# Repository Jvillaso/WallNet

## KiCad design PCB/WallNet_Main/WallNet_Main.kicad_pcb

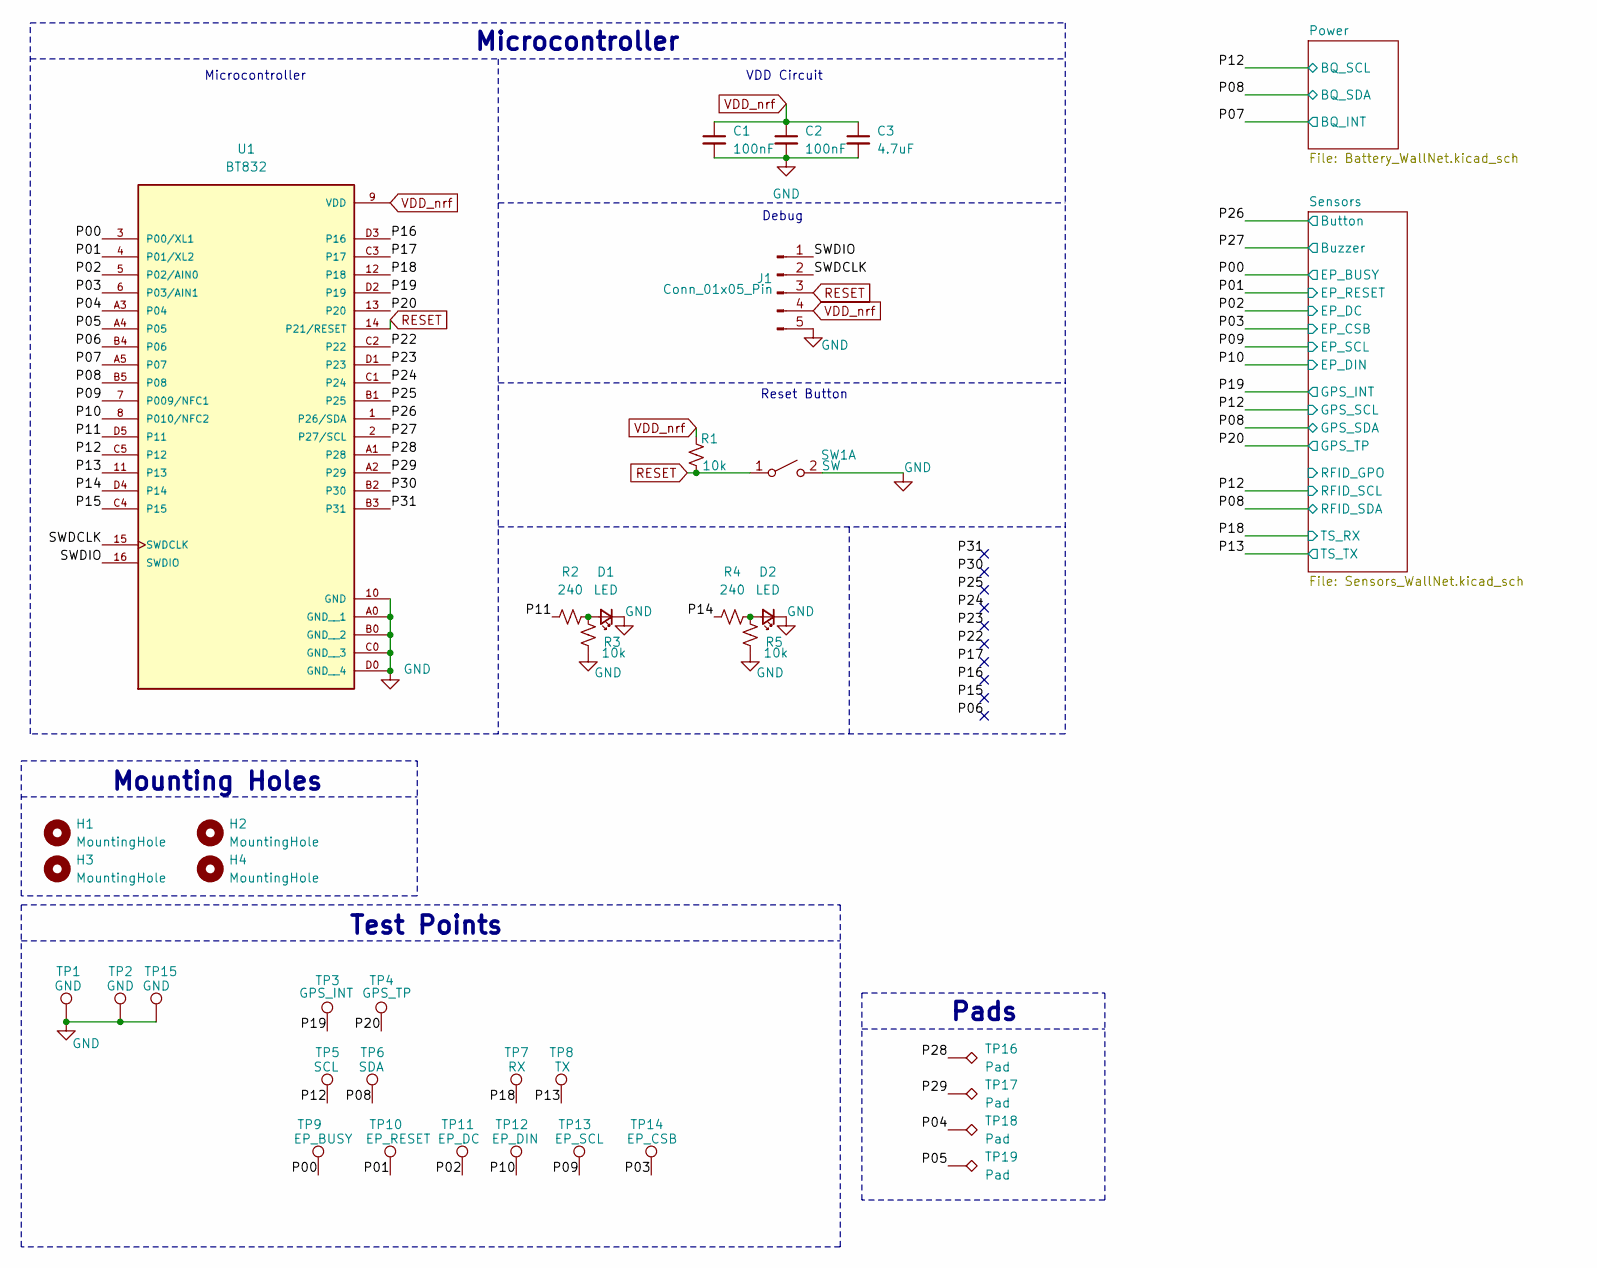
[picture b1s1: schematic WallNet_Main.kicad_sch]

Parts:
C1, C2: 100nF; C_0603_1608Metric
C3: 4.7uF; C_0805_2012Metric
D1, D2: LED; D_0603_1608Metric
H1, H2, H3, H4: MountingHole; MountingHole_4.3mm_M4
J1: Conn_01x05_Pin; PinHeader_1x05_P2.54mm_Vertical
R1, R3, R5: 10k; R_0603_1608Metric
R2, R4: 240; R_0603_1608Metric
SW1: SW; SW_Push_1P1T_NO_E-Switch_TL3301NxxxxxG
TP1: GND; TestPoint_Pad_D1.0mm
TP2, TP15: GND; KEYSTONE_5001
TP3: GPS_INT; KEYSTONE_5001
TP4: GPS_TP; KEYSTONE_5001
TP5: SCL; KEYSTONE_5001
TP6: SDA; KEYSTONE_5001
TP7: RX; KEYSTONE_5001
TP8: TX; KEYSTONE_5001
TP9: EP_BUSY; KEYSTONE_5001
TP10: EP_RESET; KEYSTONE_5001
TP11: EP_DC; KEYSTONE_5001
TP12: EP_DIN; KEYSTONE_5001
TP13: EP_SCL; KEYSTONE_5001
TP14: EP_CSB; KEYSTONE_5001
TP16, TP17, TP18, TP19: Pad; TestPoint_Pad_1.0x1.0mm
U1: BT832; BLEMODULE_BT832; PARTREV 2.04

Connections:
/P00: TP9.1, U1.3 (P00/XL1); also elsewhere on the board
/P01: TP10.1, U1.4 (P01/XL2); also elsewhere on the board
/P02: TP11.1, U1.5 (P02/AIN0); also elsewhere on the board
/P03: TP14.1, U1.6 (P03/AIN1); also elsewhere on the board
/P04: TP18.1, U1.A3 (P04)
/P05: TP19.1, U1.A4 (P05)
/P06: U1.B4 (P06)
/P07: U1.A5 (P07); also elsewhere on the board
/P08: TP6.1, U1.B5 (P08); also elsewhere on the board
/P09: TP13.1, U1.7 (P009/NFC1); also elsewhere on the board
/P10: TP12.1, U1.8 (P010/NFC2); also elsewhere on the board
/P11: R2.1, U1.D5 (P11)
/P12: TP5.1, U1.C5 (P12); also elsewhere on the board
/P13: TP8.1, U1.11 (P13); also elsewhere on the board
/P14: R4.1, U1.D4 (P14)
/P15: U1.C4 (P15)
/P16: U1.D3 (P16)
/P17: U1.C3 (P17)
/P18: TP7.1, U1.12 (P18); also elsewhere on the board
/P19: TP3.1, U1.D2 (P19); also elsewhere on the board
/P20: TP4.1, U1.13 (P20); also elsewhere on the board
/P22: U1.C2 (P22)
/P23: U1.D1 (P23)
/P24: U1.C1 (P24)
/P25: U1.B1 (P25)
/P26: U1.1 (P26/SDA); also elsewhere on the board
/P27: U1.2 (P27/SCL); also elsewhere on the board
/P28: TP16.1, U1.A1 (P28)
/P29: TP17.1, U1.A2 (P29)
/P30: U1.B2 (P30)
/P31: U1.B3 (P31)
/SWDCLK: J1.2, U1.15 (SWDCLK)
/SWDIO: J1.1, U1.16 (SWDIO)
GND: C1.2, C2.2, C3.2, D1.1 (K), D2.1 (K), J1.5, R3.1, R5.1, SW1.2 (B), TP1.1, TP2.1, TP15.1, U1.10 (GND), U1.A0 (GND__1), U1.B0 (GND__2), U1.C0 (GND__3), U1.D0 (GND__4); also elsewhere on the board
unnamed: D1.2 (A), R2.2, R3.2
unnamed: D2.2 (A), R4.2, R5.2
RESET: J1.3, R1.2, SW1.1 (A), U1.14 (P21/RESET); also elsewhere on the board
VDD_nrf: C1.1, C2.1, C3.1, J1.4, R1.1, U1.9 (VDD); also elsewhere on the board

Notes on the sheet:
Mounting Holes
Debug
Microcontroller
VDD Circuit
Test Points
Pads
Reset Button
Microcontroller

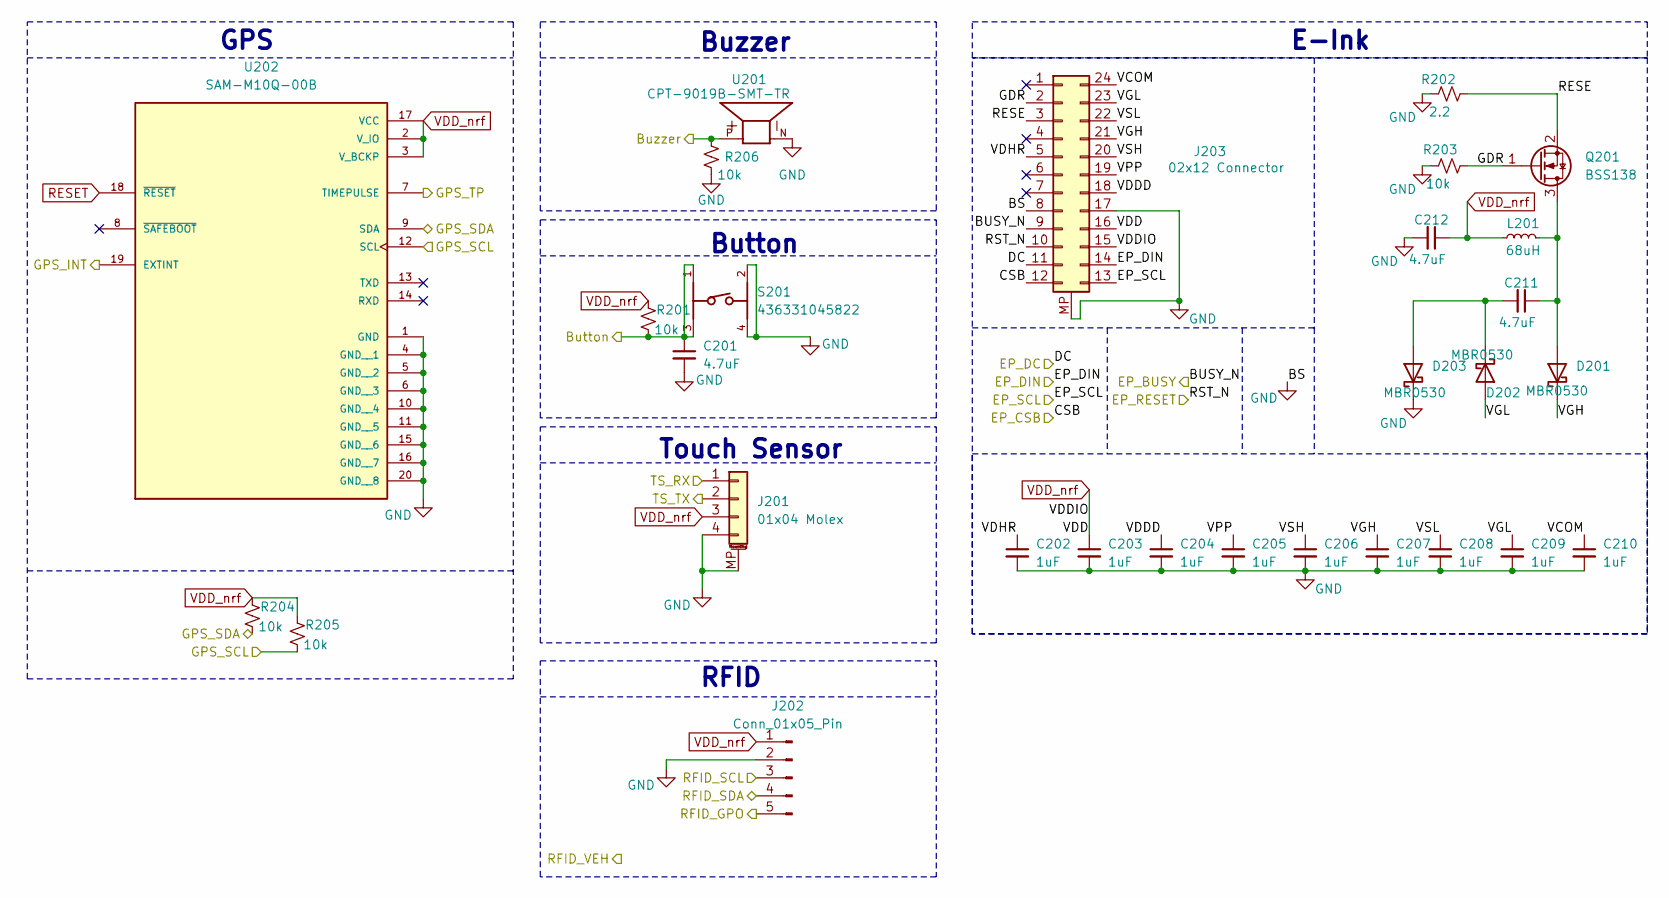
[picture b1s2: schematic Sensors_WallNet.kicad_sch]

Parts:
C201, C211, C212: 4.7uF; C_0603_1608Metric
C202, C203, C204, C205, C206, C207, C208, C209, C210: 1uF; C_0603_1608Metric
D201, D202, D203: MBR0530; D_SOD-123
J201: 01x04 Molex; Molex_PicoBlade_53261-0471_1x04-1MP_P1.25mm_Horizontal
J202: Conn_01x05_Pin; PinHeader_1x05_P2.54mm_Vertical
J203: 02x12 Connector; Amphenol_F32Q-1A7x1-11024_1x24-1MP_P0.5mm_Horizontal
L201: 68uH; IND_VLS3015CX-680M-H
Q201: BSS138; SOT-23
R201, R203, R204, R205, R206: 10k; R_0603_1608Metric
R202: 2.2; R_0603_1608Metric
S201: 436331045822; 4363X10458XX
U201: CPT-9019B-SMT-TR; XDCR_CPT-9019B-SMT-TR; PARTREV 1.0
U202: SAM-M10Q-00B; XCVR_SAM-M10Q-00B; PARTREV R03

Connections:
/P00: J203.9; also elsewhere on the board
/P01: J203.10; also elsewhere on the board
/P02: J203.11; also elsewhere on the board
/P03: J203.12; also elsewhere on the board
/P08: J202.4, R204.2, U202.9 (SDA); also elsewhere on the board
/P09: J203.13; also elsewhere on the board
/P10: J203.14; also elsewhere on the board
/P12: J202.3, R205.2, U202.12 (SCL); also elsewhere on the board
/P13: J201.2; also elsewhere on the board
/P18: J201.1; also elsewhere on the board
/P19: U202.19 (EXTINT); also elsewhere on the board
/P20: U202.7 (TIMEPULSE); also elsewhere on the board
/P26: C201.1, R201.2, S201.1, S201.3; also elsewhere on the board
/P27: R206.1, U201.P; also elsewhere on the board
/Sensors/GDR: J203.2, Q201.1 (G), R203.2
/Sensors/RESE: J203.3, Q201.2 (S), R202.2
/Sensors/RFID_GPO: J202.5
/Sensors/VCOM: C210.1, J203.24
/Sensors/VDDD: C204.1, J203.18
/Sensors/VDHR: C202.1, J203.5
/Sensors/VGH: C207.1, D201.1 (K), J203.21
/Sensors/VGL: C209.1, D202.2 (A), J203.23
/Sensors/VPP: C205.1, J203.19
/Sensors/VSH: C206.1, J203.20
/Sensors/VSL: C208.1, J203.22
GND: C201.2, C202.2, C203.2, C204.2, C205.2, C206.2, C207.2, C208.2, C209.2, C210.2, C212.2, D203.1 (K), J201.4, J201.MP (MountPin), J202.2, J203.8, J203.17, J203.MP (Pin_12), R202.1, R203.1, R206.2, S201.2, S201.4, U201.N, U202.1 (GND), U202.4 (GND__1), U202.5 (GND__2), U202.6 (GND__3), U202.10 (GND__4), U202.11 (GND__5), U202.15 (GND__6), U202.16 (GND__7), U202.20 (GND__8); also elsewhere on the board
unnamed: C211.1, D201.2 (A), L201.2, Q201.3 (D)
unnamed: C211.2, D202.1 (K), D203.2 (A)
RESET: U202.18 (~RESET); also elsewhere on the board
VDD_nrf: C203.1, C212.1, J201.3, J202.1, J203.15, J203.16, L201.1, R201.1, R204.1, R205.1, U202.2 (V_IO), U202.3 (V_BCKP), U202.17 (VCC); also elsewhere on the board

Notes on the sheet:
RFID
E-Ink
GPS
Button
Touch Sensor
Buzzer

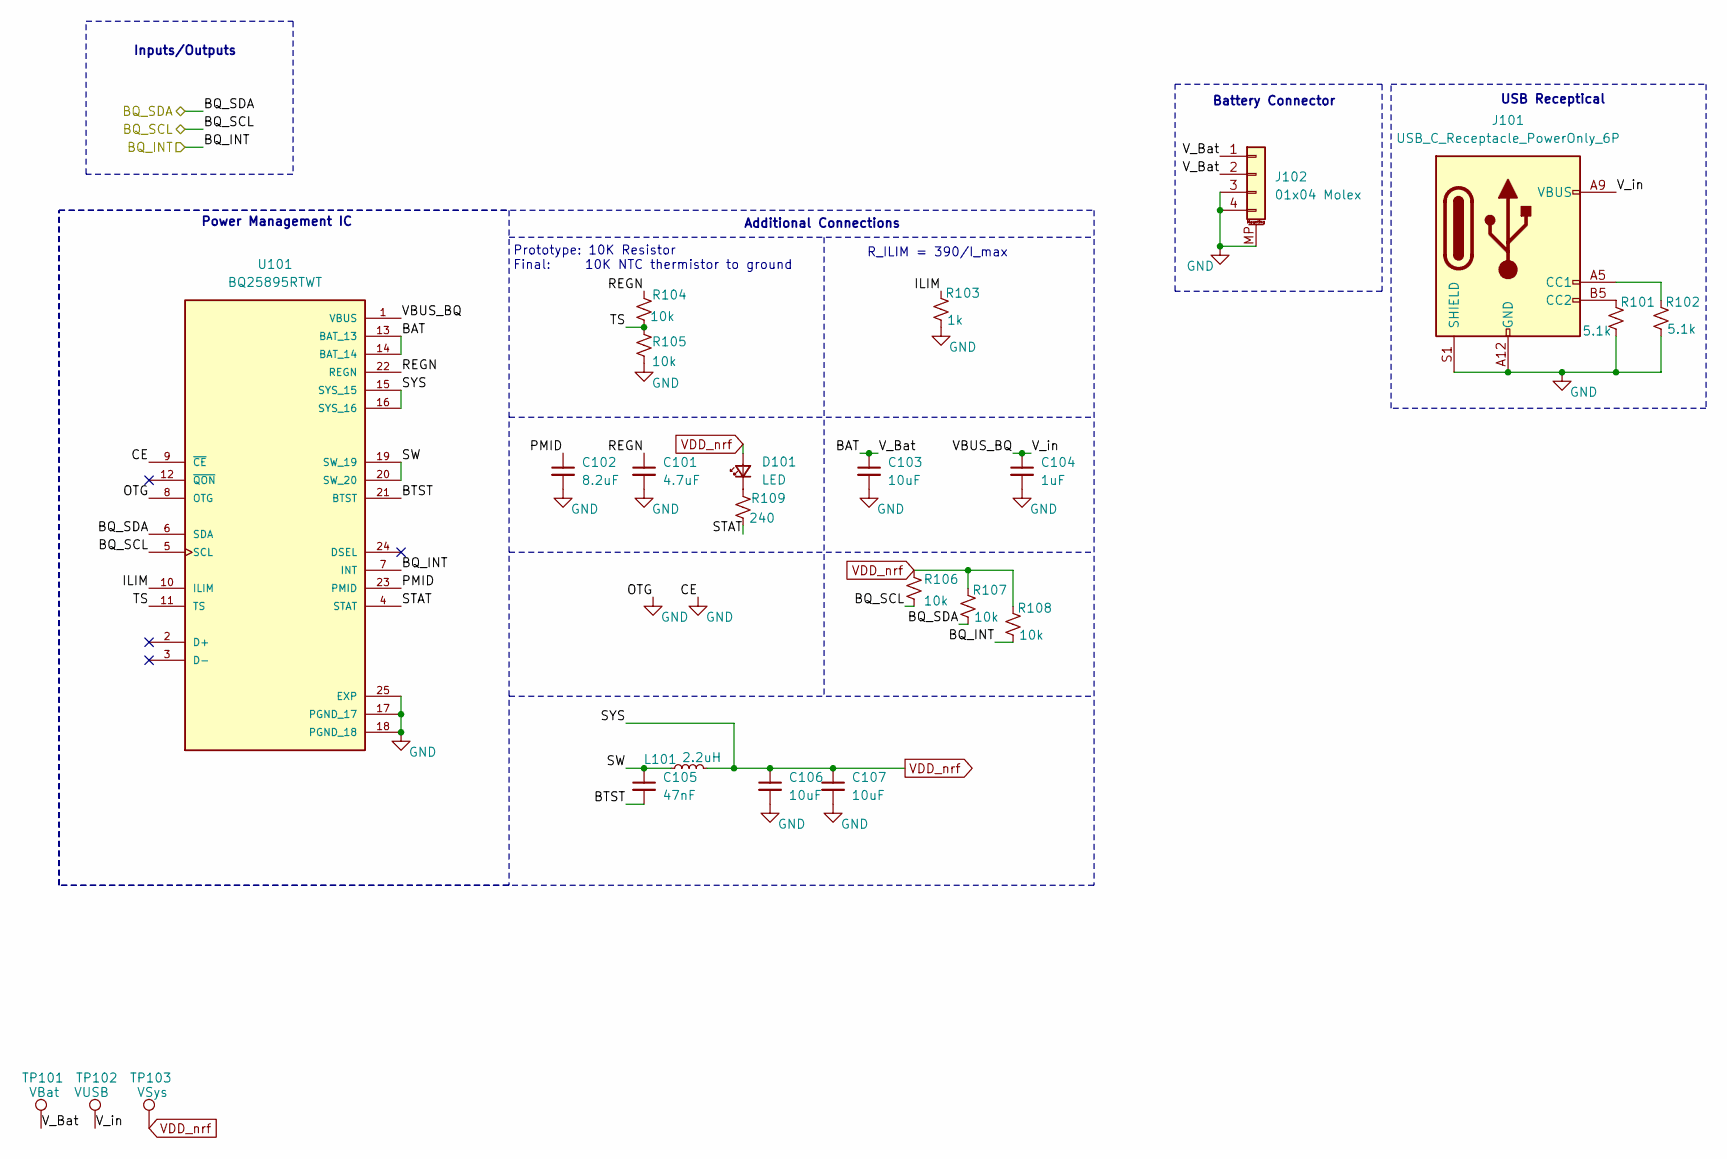
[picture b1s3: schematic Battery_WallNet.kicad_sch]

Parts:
C101: 4.7uF; C_0603_1608Metric
C102: 8.2uF; C_0805_2012Metric
C103: 10uF; C_0805_2012Metric
C104: 1uF; C_0603_1608Metric
C105: 47nF; C_0603_1608Metric
C106, C107: 10uF; C_0603_1608Metric
D101: LED; D_0603_1608Metric
J101: USB_C_Receptacle_PowerOnly_6P; USB_C_Receptacle_GCT_USB4125-xx-x-0190_6P_TopMnt_Horizontal
J102: 01x04 Molex; Molex_PicoBlade_53261-0471_1x04-1MP_P1.25mm_Horizontal
L101: 2.2uH; IND_IMSC1008AZER_VIS
R101, R102: 5.1k; R_0603_1608Metric
R103: 1k; R_0603_1608Metric
R104, R105, R106, R107, R108: 10k; R_0603_1608Metric
R109: 240; R_0603_1608Metric
TP101: VBat; TestPoint_Pad_D1.0mm
TP102: VUSB; TestPoint_Pad_D1.0mm
TP103: VSys; TestPoint_Pad_D1.0mm
U101: BQ25895RTWT; Texas_RTW_WQFN-24-1EP_4x4mm_P0.5mm_EP2.7x2.7mm; PARTREV B

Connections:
/P07: R108.2, U101.7 (INT); also elsewhere on the board
/P08: R107.2, U101.6 (SDA); also elsewhere on the board
/P12: R106.2, U101.5 (SCL); also elsewhere on the board
/Power/BAT: C103.1, J102.1, J102.2, TP101.1, U101.13 (BAT_13), U101.14 (BAT_14)
/Power/BTST: C105.2, U101.21 (BTST)
/Power/ILIM: R103.1, U101.10 (ILIM)
/Power/PMID: C102.1, U101.23 (PMID)
/Power/REGN: C101.1, R104.1, U101.22 (REGN)
/Power/STAT: R109.2, U101.4 (STAT)
/Power/SW: C105.1, L101.1, U101.19 (SW_19), U101.20 (SW_20)
/Power/TS: R104.2, R105.1, U101.11 (TS)
/Power/VBUS_BQ: C104.1, J101.A9 (VBUS), J101.B9 (VBUS), TP102.1, U101.1 (VBUS)
GND: C101.2, C102.2, C103.2, C104.2, C106.2, C107.2, J101.A12 (GND), J101.B12 (GND), J101.S1 (SHIELD), J102.3, J102.4, J102.MP (MountPin), R101.2, R102.2, R103.2, R105.2, U101.8 (OTG), U101.9 (~CE), U101.17 (PGND_17), U101.18 (PGND_18), U101.25 (EXP); also elsewhere on the board
unnamed: D101.1 (K), R109.1
unnamed: J101.A5 (CC1), R102.1
unnamed: J101.B5 (CC2), R101.1
VDD_nrf: C106.1, C107.1, D101.2 (A), L101.2, R106.1, R107.1, R108.1, TP103.1, U101.15 (SYS_15), U101.16 (SYS_16); also elsewhere on the board

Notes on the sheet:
Battery Connector
USB Receptical
Prototype: 10K Resistor Final: 10K NTC thermistor to ground
Additional Connections
Power Management IC
R_ILIM = 390/I_max
Inputs/Outputs

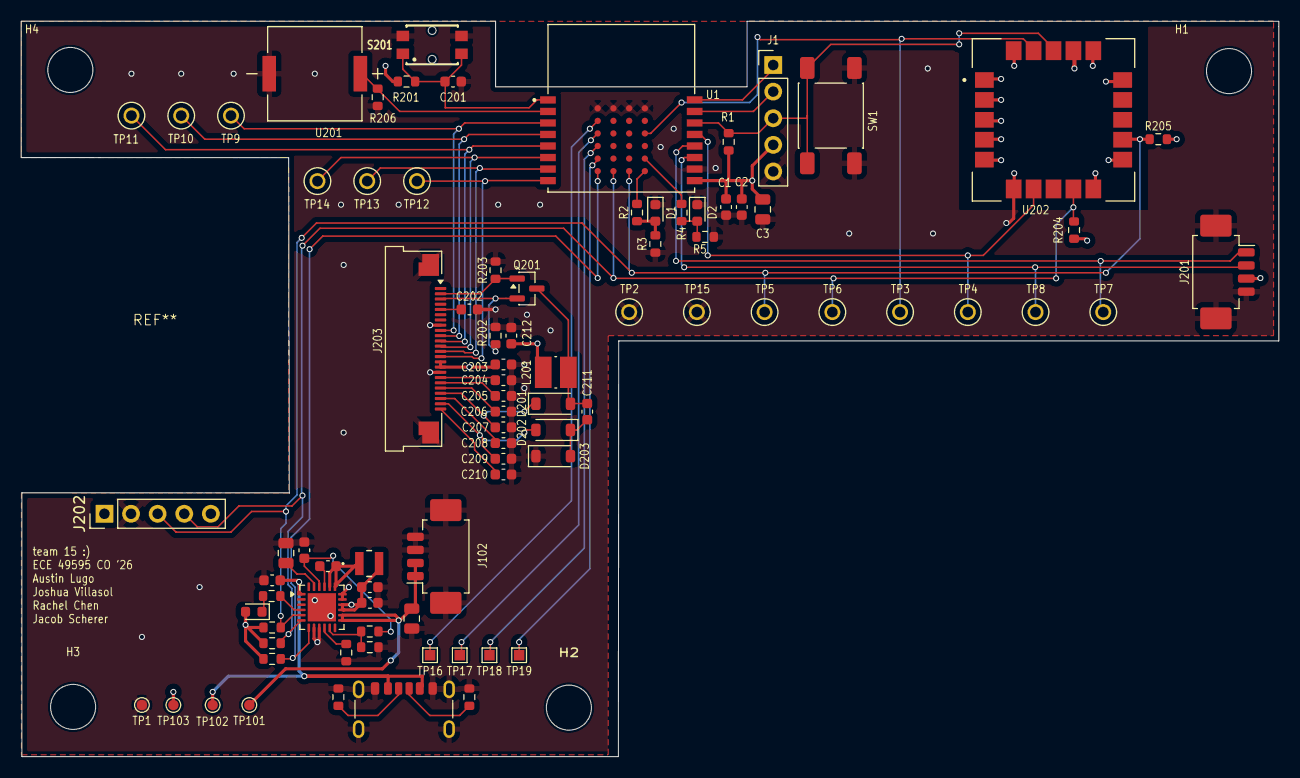
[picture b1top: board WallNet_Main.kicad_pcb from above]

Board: 4 copper layers, 120.0 x 70.2 mm, 89 parts (0 on the bottom side), 52 nets.

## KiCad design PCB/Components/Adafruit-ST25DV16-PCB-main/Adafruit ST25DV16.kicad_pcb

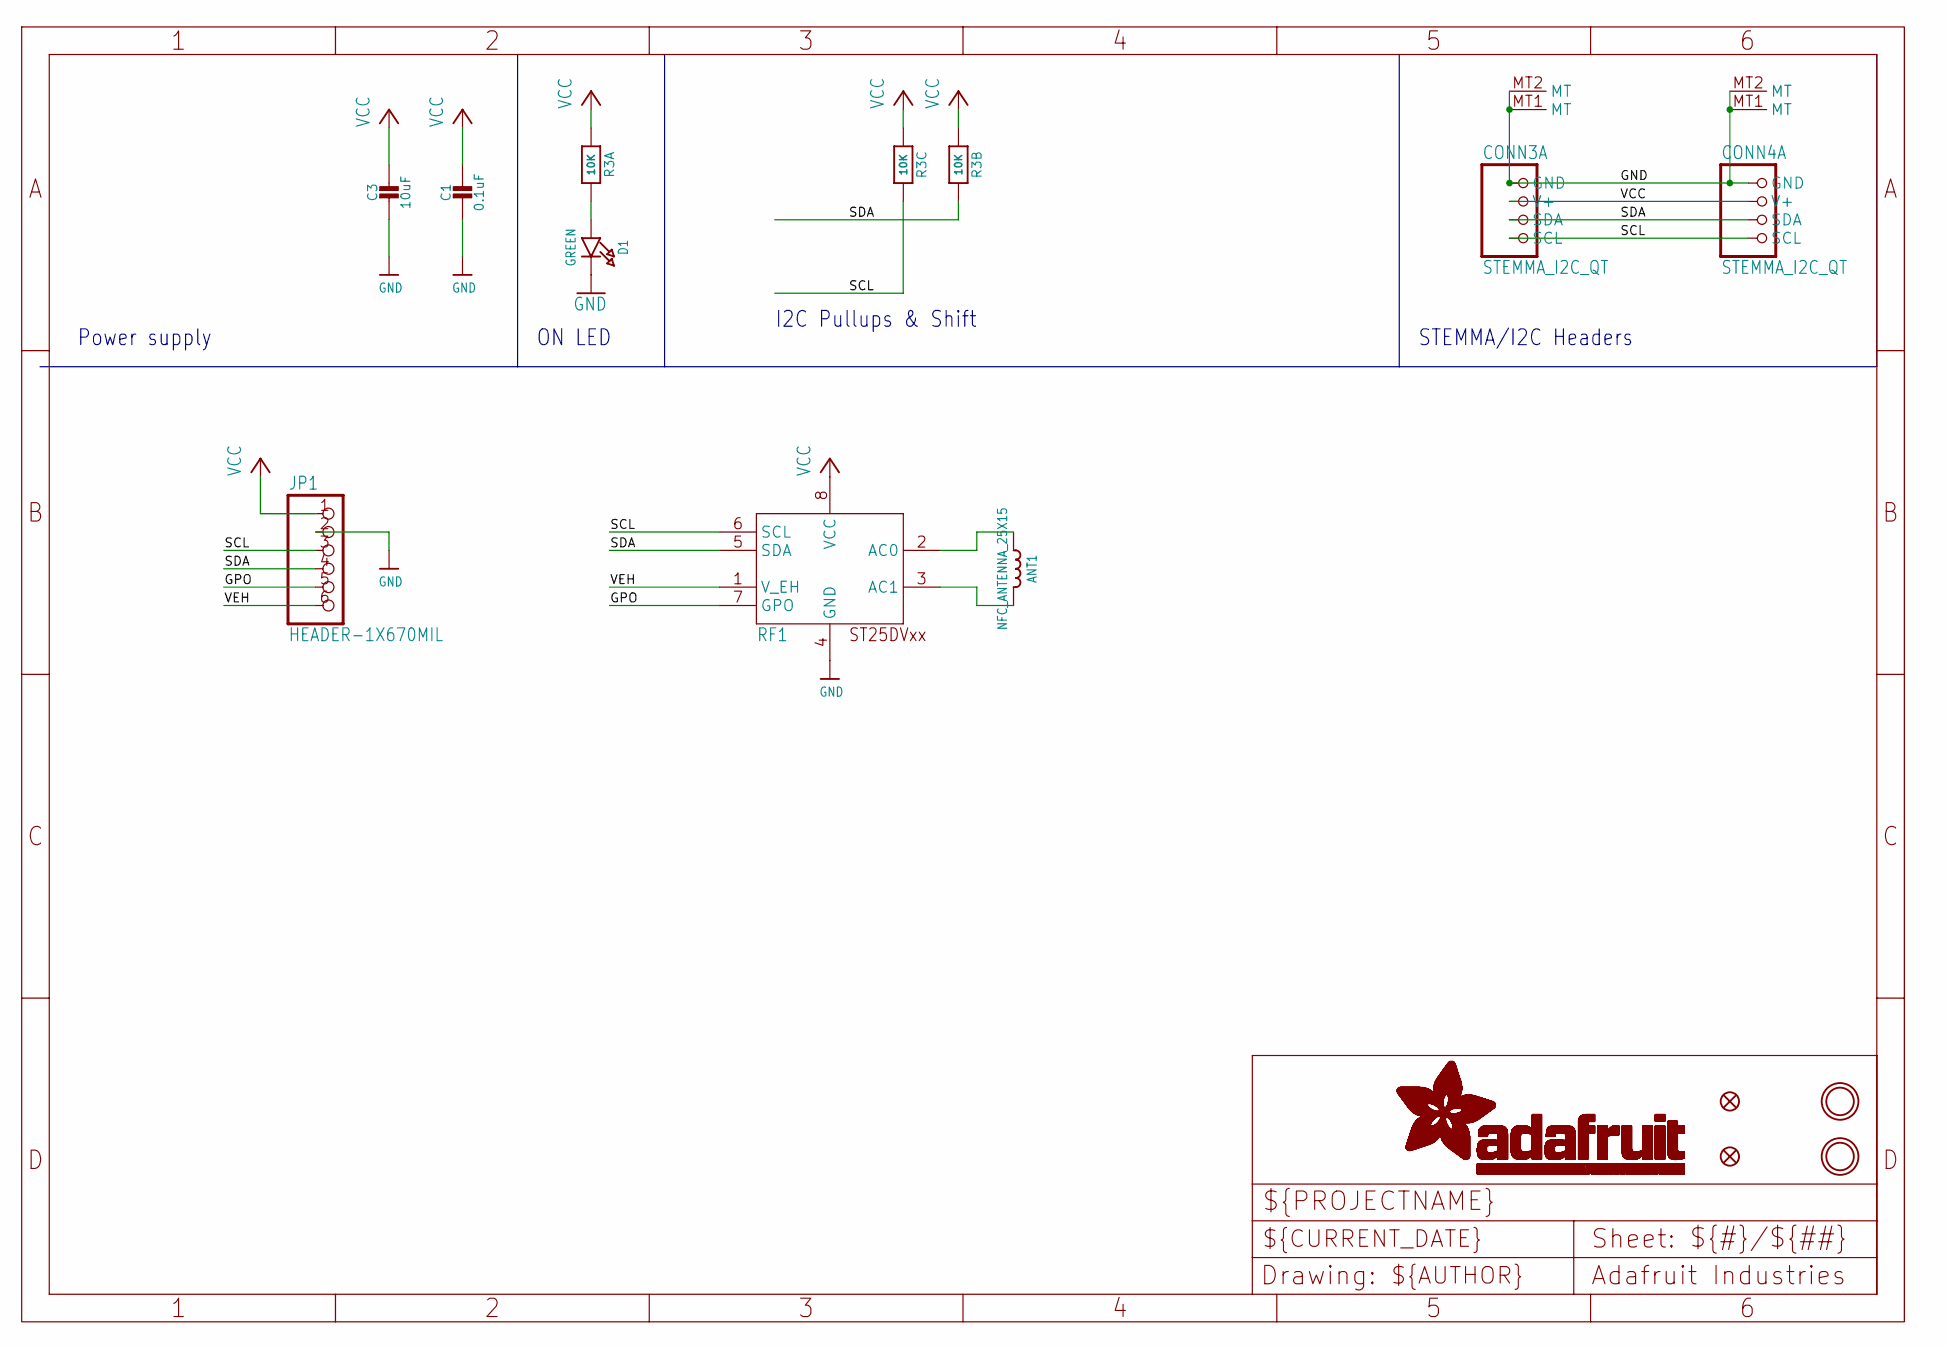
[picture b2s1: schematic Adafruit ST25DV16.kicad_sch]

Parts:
ANT1: NFC_ANTENNA_25X15; NFCANT_25X15
C1: 0.1uF; 0603-NO
C3: 10uF; 0805-NO
CONN3, CONN4: STEMMA_I2C_QT; JST_SH4
D1: GREEN; CHIPLED_0603_NOOUTLINE
FID3, FID4: FIDUCIAL_1MM
JP1: HEADER-1X670MIL; 1X06_ROUND_70
R3: 10K; RESPACK_4X0603
RF1: ST25DVXX_TSSOP; TSSOP8-4.4MM
U$19, U$21: MOUNTINGHOLE2.5; MOUNTINGHOLE_2.5_PLATED

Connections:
GND: C1.2, C3.2, CONN3.1 (GND), CONN3.MT1 (MT), CONN3.MT2 (MT), CONN4.1 (GND), CONN4.MT1 (MT), CONN4.MT2 (MT), D1.C, JP1.2, RF1.4 (GND)
GPO: JP1.5, RF1.7 (GPO)
unnamed: D1.A, R3.8 (2)
unnamed: ANT1.P$2 (2), RF1.2 (AC0)
unnamed: ANT1.P$1 (1), RF1.3 (AC1)
SCL: CONN3.4 (SCL), CONN4.4 (SCL), JP1.3, R3.6 (2), RF1.6 (SCL)
SDA: CONN3.3 (SDA), CONN4.3 (SDA), JP1.4, R3.7 (2), RF1.5 (SDA)
VCC: C1.1, C3.1, CONN3.2 (V+), CONN4.2 (V+), JP1.1, R3.1, R3.2 (1), R3.3 (1), RF1.8 (VCC)
VEH: JP1.6, RF1.1 (V_EH)

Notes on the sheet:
Power supply
ON LED
STEMMA/I2C Headers
I2C Pullups & Shift

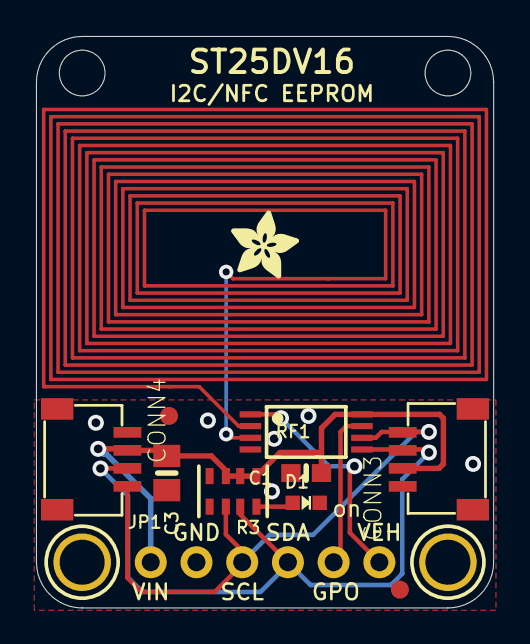
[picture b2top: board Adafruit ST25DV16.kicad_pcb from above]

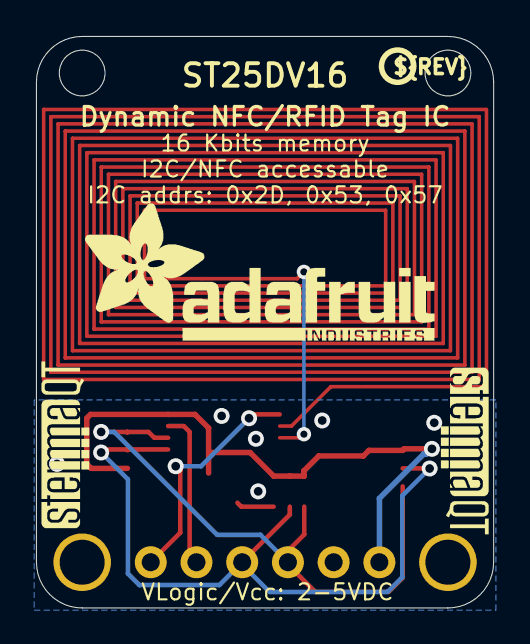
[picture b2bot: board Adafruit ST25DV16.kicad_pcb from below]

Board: 2 copper layers, 25.4 x 31.8 mm, 20 parts (4 on the bottom side), 9 nets.

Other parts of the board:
U$1: ADAFRUIT_TEXT_20MM
U$22: ADAFRUIT_3.5MM
U$25: PCBFEAT-REV-040
U$30, U$31: STEMMAQT
UNK_HOLE_0: dummyfp0
UNK_HOLE_1: dummyfp1

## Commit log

2026-01-26 Initial Commit
    Added PCB and a few main folders
2026-01-26 Changed Microcontroller
2026-01-26 Commit microcontroller
2026-02-03 Power Management Finished
2026-02-03 bruh
2026-02-04 Added app/esp32 files
2026-02-04 Changed some Heir connections
2026-02-05 E-ink & GPS connection Complete
2026-02-06 Parts complete for schematic
2026-02-08 Schematic done, updated layout
2026-02-09 Manager Meeting Updates
2026-02-09 Added battery hole
    Changed layout to include a hole for the battery (with 1mm more than the documentation says on either side. Maybe make more room?)
2026-02-11 added debug LED
2026-02-11 changed minor
2026-02-12 "changed small things"
2026-02-13 "added test point debugging and mounting holes"
2026-02-13 Updated, Schematic done, waiting on Layout
2026-02-13 Updated fp interface
2026-02-13 Placed components on board
2026-02-13 Added some of the power traces
2026-02-14 Added more traces for power
2026-02-15 Finished wiring up BMU/PWR system
2026-02-15 updated connectors, added layout guide
2026-02-15 random
2026-02-15 Reordered the parts, battery in corner, and added discreet parts next to the plug in for eink
2026-02-15 some random changes
2026-02-15 Added discreet components around BMU
2026-02-16 finished layout of pcb
2026-02-16 sum stuff?
2026-02-16 Accident
2026-02-16 Revert "finished layout of pcb"
    This reverts commit 3cbfe1fb2af5c7caebbb8541d969812e7f94bd95.
    Yea man
2026-02-16 done with data lines, only need power vias
2026-02-16 test?
2026-02-16 updated version with my actual pcb
2026-02-16 added power and fixed errors
2026-02-16 added RFID model
2026-02-17 Finished adding cutout, via, and mount hole for RFID
2026-02-17 Wallnet presentable design. added extra folder for current submision
2026-02-18 Redid PCB still need to DRC the design
2026-02-19 Finish layout
2026-02-23 Fixed minor Issues
2026-02-23 added new mit app inventor file
2026-02-24 added some code for bluetooth but still need to make work
2026-02-26 Made wallnet app talk with nrf
2026-02-27 Fixed position of mounting holes
2026-02-28 quick change
2026-03-09 some changes to nrf code
2026-03-09 Implemented most changes
2026-03-09 Add gps over UART test files, should work for general UART comm. if CONFIG_GPS_PARSED_OUTPUT=n set
2026-03-12 Acute angles destroyed
2026-03-12 added
2026-03-20 some experimenting with gps
2026-03-23 Some stuff
2026-03-24 Moved around some folders
2026-03-24 committing ble folder
2026-03-31 New app version - added card add/send over ble
2026-04-01 Added enrollment/identify to nrf fp file
2026-04-01 Added enrollment/identify
2026-04-06 Added fp folder
2026-04-07 Maybe adding fp files?
2026-04-08 packaging 1st pass
2026-04-10 Added some changes to make the fit better
2026-04-11 Packaging v3
2026-04-11 Edited the size of the button extender
2026-04-12 added a bom
2026-04-12 finger enrollment accepts multiple finger taps
2026-04-12 new meshes
2026-04-12 App update - idr what changed
2026-04-12 first software integration draft
2026-04-12 changed top of packaging and in app, hid the card info from the BLE connection
2026-04-12 Added updated fp files to WallNet_1
2026-04-13 Included code
2026-04-13 Stop tracking build files in WallNet_1
2026-04-13 GPS integrated and working as a constant poll
2026-04-14 First prototype of fp integration, not on work schedule yet
2026-04-14 fixed bug where sending data caused BLE to disconnect. Also added test module to print all packets sent to a char
2026-04-14 Added some packet sending (To be tested) and support for new testing characteristic
2026-04-14 Fingerprint working, authenticating, and multiple enrollment
2026-04-15 Added packets for card sending
2026-04-15 Finished packet sending of cc information
2026-04-15 update card handling
2026-04-15 made room for flywire
2026-04-16 update display states, dont scan fp when 0 cards, stop scanning during card saving
2026-04-16 Fixed fingerpint timing for enrollment/id after enrollment
2026-04-16 Adjusted fp timing/fp score
2026-04-16 added rfid
2026-04-16 rachel nrf
2026-04-16 Added code for toggling. Need to test still
2026-04-16 added buzzer support
2026-04-16 Rachel stuff
2026-04-20 added some debouncing changes and made logging for errors in app
2026-04-21 Changed top of packaging and played around with buzzer code
2026-04-21 Added buzzer succesfully!
2026-04-21 Fix fingerprint scanning loop and add spot to save cards/wallet to nrf nvm
2026-04-21 Save fingerprint count/cards to NVM
2026-04-21 adeed mit app inventor extensions and started on a folder for SPI
2026-04-22 RFID integration started -- rfid packet it built, i2c1 configured: Moving on to build/write link
2026-04-22 rfid integration stuff
2026-04-22 rfid
2026-04-22 fully working link ndef writes
2026-04-22 Working RFID Integration
2026-04-22 More Card Validation
2026-04-23 gps/rfid working on i2c1 bus together - i2c0 left for BMU
2026-04-23 added hello
2026-04-23 EINK WORKS
2026-04-23 Finished writing a card to eink
2026-04-23 wrote conversion for bq
2026-04-23 added error messages but need to clear them
2026-04-23 added "clearing" of errors
2026-04-23 got eink working on integrated code
2026-04-23 integrated eink with Wallnet_1
2026-04-23 battery start
2026-04-23 bq hi
2026-04-23 Start bq integration
2026-04-23 show battery
2026-04-24 pin changes
2026-04-24 ignore build files
2026-04-24 Eink integrated
2026-04-24 Eink dir working
2026-04-24 bq scheduling code
